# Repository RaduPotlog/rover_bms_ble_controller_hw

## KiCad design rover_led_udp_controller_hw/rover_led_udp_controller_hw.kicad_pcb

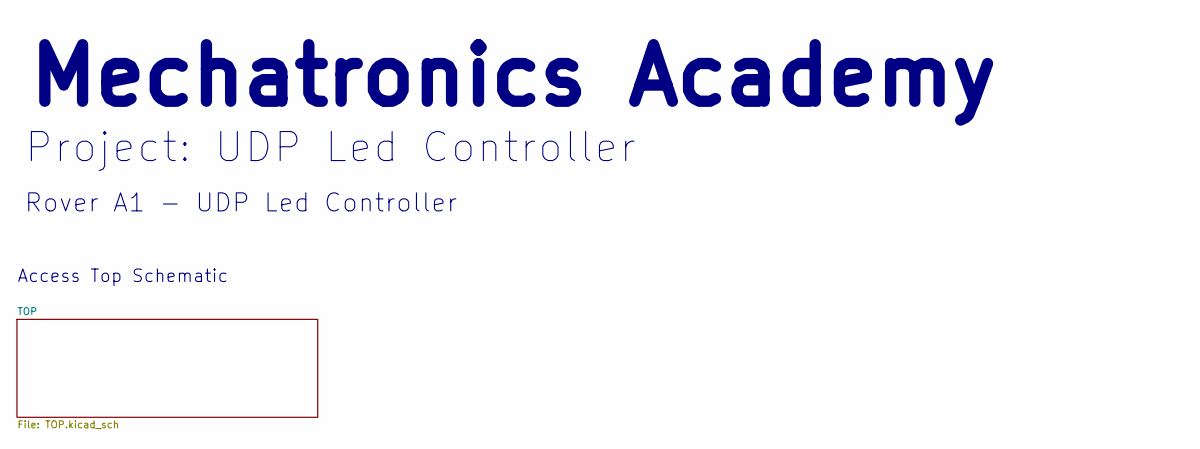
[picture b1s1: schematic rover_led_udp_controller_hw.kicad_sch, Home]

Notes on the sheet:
Rover A1 - UDP Led Controller
Project: UDP Led Controller
Access Top Schematic
Mechatronics Academy

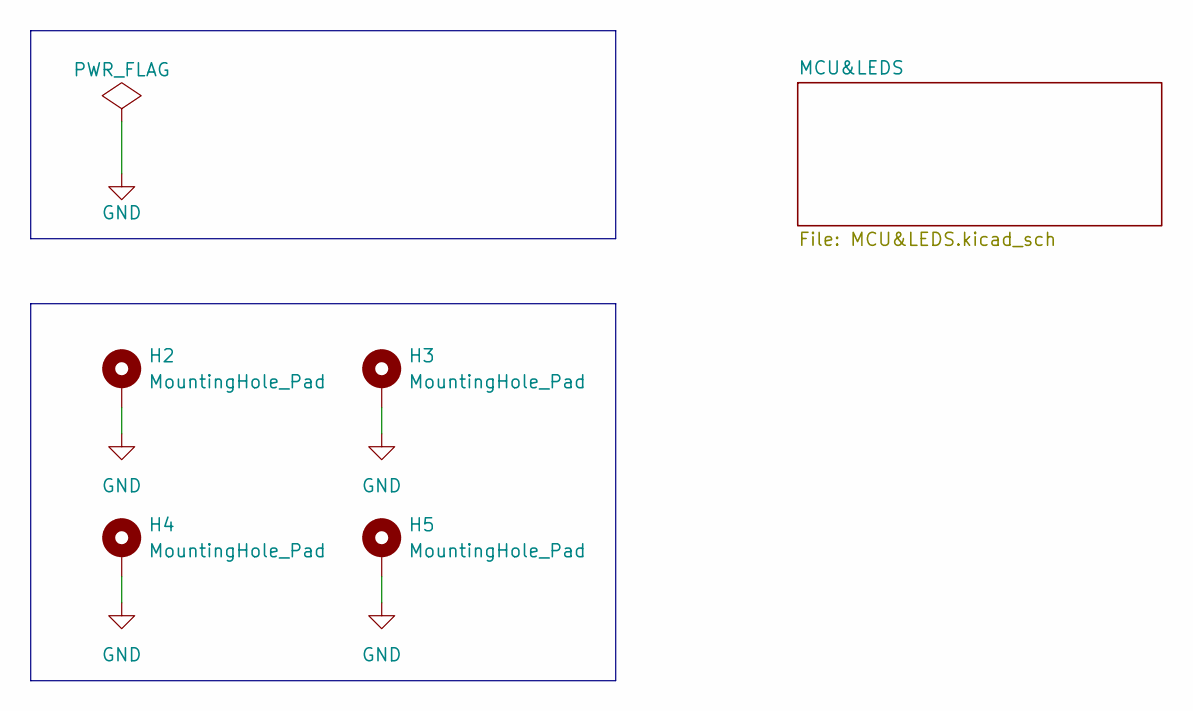
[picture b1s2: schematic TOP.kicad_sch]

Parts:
H2, H3, H4, H5: MountingHole_Pad; MountingHole_2.5mm_Pad_Via

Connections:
GND: H2.1 (1_1), H3.1 (1_1), H4.1 (1_1), H5.1 (1_1); also elsewhere on the board

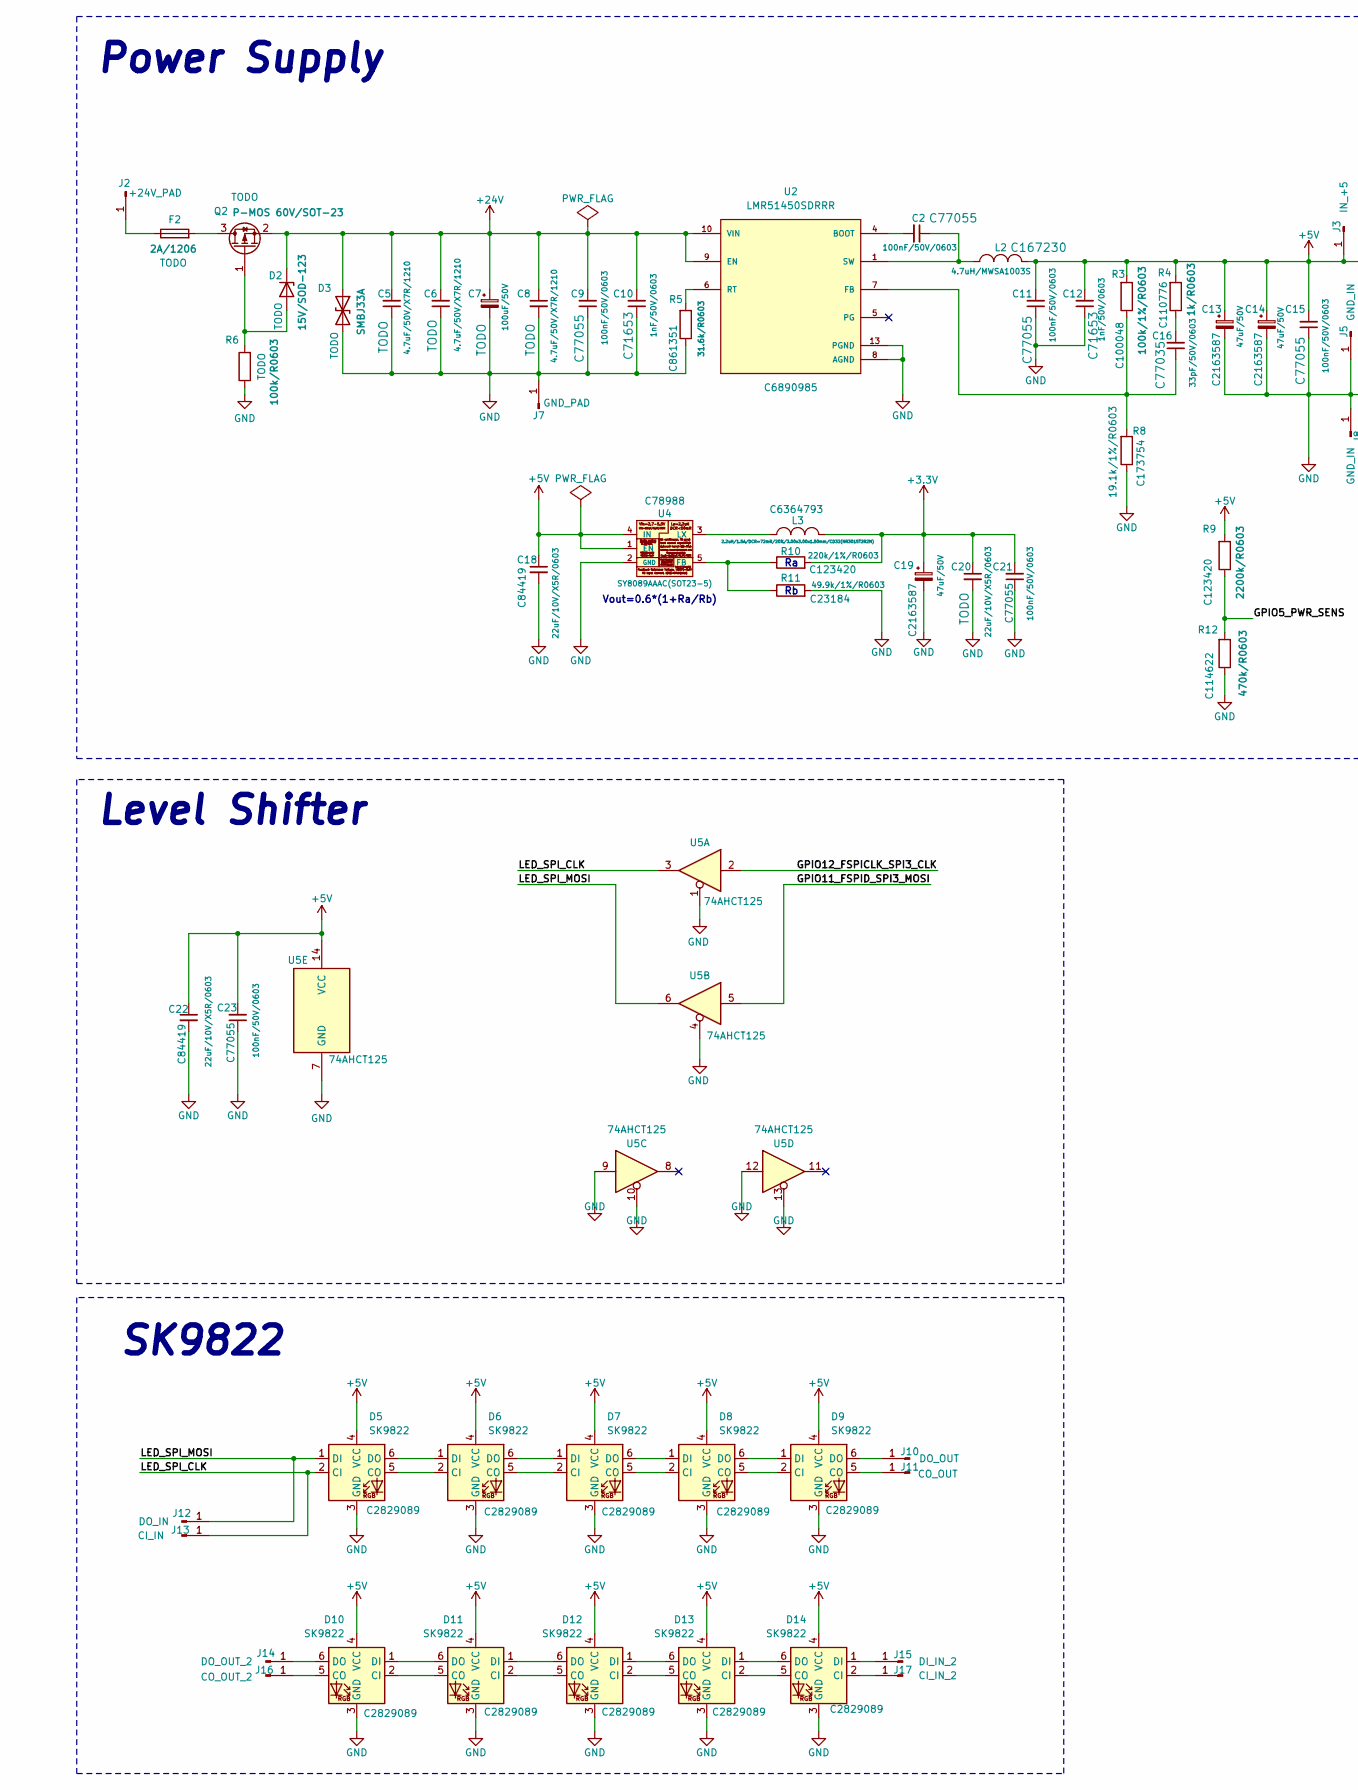
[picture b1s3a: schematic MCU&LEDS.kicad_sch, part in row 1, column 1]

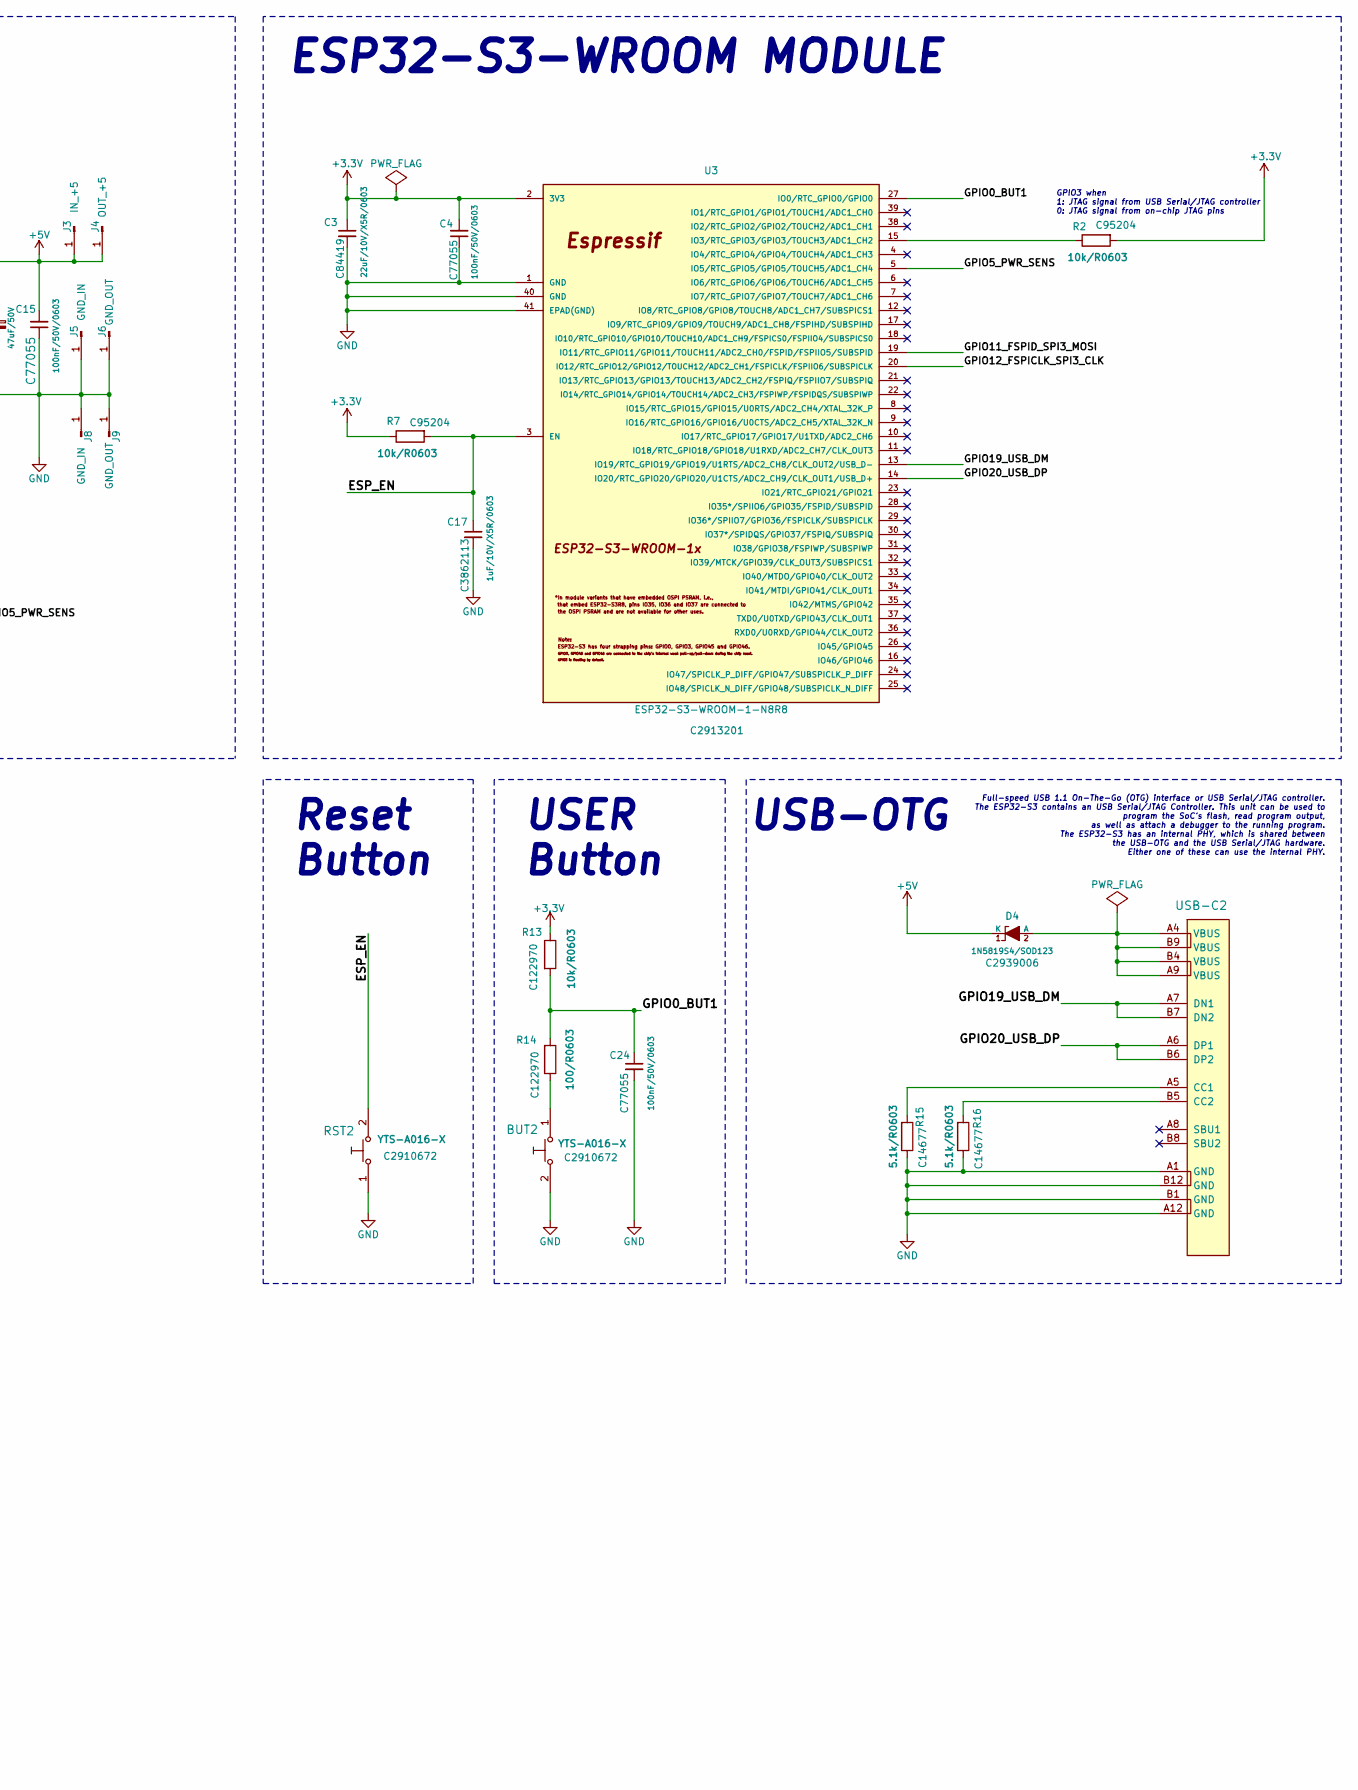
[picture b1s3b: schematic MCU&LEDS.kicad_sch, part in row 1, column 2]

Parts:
BUT2: YTS-A016-X; JLCPCB C2910672
C2, C4, C9, C11, C15, C21, C23, C24: 100nF/50V/0603; C_0603_1608Metric; JLCPCB C77055
C3, C18, C22: 22uF/10V/X5R/0603; C_0603_1608Metric; JLCPCB C84419
C5, C6, C8: 4.7uF/50V/X7R/1210; C_1210_3225Metric; JLCPCB TODO
C7: 100uF/50V; CP_Elec_8x10.5; JLCPCB TODO
C10, C12: 1nF/50V/0603; C_0603_1608Metric; JLCPCB C71653
C13, C14, C19: 47uF/50V; CP_Elec_6.3x7.7; JLCPCB C2163587
C16: 33pF/50V/0603; C_0603_1608Metric; JLCPCB C77035
C17: 1uF/10V/X5R/0603; C_0603_1608Metric; JLCPCB C3862113
C20: 22uF/10V/X5R/0603; C_0603_1608Metric; JLCPCB TODO
D2: 15V/SOD-123; D_SOD-123; JLCPCB TODO
D3: SMBJ33A; D_SMB; JLCPCB TODO
D4: 1N5819S4/SOD123; SOD-123_1C-2A_KA; JLCPCB C2939006
D5, D6, D7, D8, D9, D10, D11, D12, D13, D14: SK9822; LED_RGB_5050-6; JLCPCB C2829089
F2: 2A/1206; Fuse_1206_3216Metric; JLCPCB TODO
J2: +24V_PAD; TestPoint_Pad_1
J3: IN_+5; TestPoint_Pad_1
J4: OUT_+5; TestPoint_Pad_1
J5, J8: GND_IN; TestPoint_Pad_1
J6, J9: GND_OUT; TestPoint_Pad_1
J7: GND_PAD; TestPoint_Pad_1
J10: DO_OUT; TestPoint_Pad
J11: CO_OUT; TestPoint_Pad
J12: DO_IN; TestPoint_Pad
J13: CI_IN; TestPoint_Pad
J14: DO_OUT_2; TestPoint_Pad
J15: DI_IN_2; TestPoint_Pad
J16: CO_OUT_2; TestPoint_Pad
J17: CI_IN_2; TestPoint_Pad
L2: 4.7uH/MWSA1003S; L_Sunlord_MWSA1003S; JLCPCB C167230
L3: 2.2uH/1.5A/DCR=72mR/20%/3.00x3.00x1.50mm/CD32(NR3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; CD32; JLCPCB C6364793
Q2: P-MOS 60V/SOT-23; SOT-23; JLCPCB TODO
R2, R7: 10k/R0603; R_0603_1608Metric_Pad0.98x0.95mm_HandSolder; JLCPCB C95204
R3: 100k/1%/R0603; R_0603_1608Metric_Pad0.98x0.95mm_HandSolder; JLCPCB C100048
R4: 1k/R0603; R_0603_1608Metric_Pad0.98x0.95mm_HandSolder; JLCPCB C110776
R5: 31.6k/R0603; R_0603_1608Metric_Pad0.98x0.95mm_HandSolder; JLCPCB C861351
R6: 100k/R0603; R_0603_1608Metric_Pad0.98x0.95mm_HandSolder; JLCPCB TODO
R8: 19.1k/1%/R0603; R_0603_1608Metric_Pad0.98x0.95mm_HandSolder; JLCPCB C173754
R9: 2200k/R0603; R_0603_1608Metric_Pad0.98x0.95mm_HandSolder; JLCPCB C123420
R10: 220k/1%/R0603; R_0603_1608Metric_Pad0.98x0.95mm_HandSolder; JLCPCB C123420
R11: 49.9k/1%/R0603; R_0603_1608Metric_Pad0.98x0.95mm_HandSolder; JLCPCB C23184
R12: 470k/R0603; R_0603_1608Metric_Pad0.98x0.95mm_HandSolder; JLCPCB C114622
R13: 10k/R0603; R_0603_1608Metric_Pad0.98x0.95mm_HandSolder; JLCPCB C122970
R14: 100/R0603; R_0603_1608Metric_Pad0.98x0.95mm_HandSolder; JLCPCB C122970
R15, R16: 5.1k/R0603; R_0603_1608Metric_Pad0.98x0.95mm_HandSolder; JLCPCB C14677
RST2: YTS-A016-X; JLCPCB C2910672
U2: LMR51450SDRRR; PARTREV December 2022; JLCPCB C6890985
U3: ESP32-S3-WROOM-1-N8R8; ESP32-­S3-­WROOM­-1; JLCPCB C2913201
U4: SY8089AAAC(SOT23-5); SOT-23-5; JLCPCB C78988
U5: 74AHCT125; SOIC-14_3.9x8.7mm_P1.27mm
USB-C2: USB2.0_TYPE-C(A40-00119-A52-12); USB2.0_TYPE-C-ONLY-PADS

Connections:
+3.3V: C3.1, C4.2, C19.1, C20.1, C21.2, L3.2, R2.2, R7.1, R10.2, R13.1, U3.2 (3V3)
+5V: C11.2, C12.2, C13.1, C14.1, C15.2, C18.1, C22.1, C23.2, D4.1 (K), D5.4 (VCC), D6.4 (VCC), D7.4 (VCC), D8.4 (VCC), D9.4 (VCC), D10.4 (VCC), D11.4 (VCC), D12.4 (VCC), D13.4 (VCC), D14.4 (VCC), J3.1 (Pin_1_1), J4.1 (Pin_1_1), L2.2, R3.2, R4.2, R9.2, U4.1 (EN), U4.4 (IN), U5.14 (VCC)
+24V: C5.2, C6.2, C7.1, C8.1, C9.2, C10.2, D2.1 (K), D3.1 (A1), Q2.2 (S), U2.9 (EN), U2.10 (VIN), U2.11 (VIN), U2.12 (VIN)
/TOP/MCU&LEDS/ESP_EN: C17.1, R7.2, RST2.2, U3.3 (EN)
/TOP/MCU&LEDS/GPIO0_BUT1: C24.1, R13.2, R14.2, U3.27 (IO0/RTC_GPIO0/GPIO0)
/TOP/MCU&LEDS/GPIO5_PWR_SENS: R9.1, R12.2, U3.5 (IO5/RTC_GPIO5/GPIO5/TOUCH5/ADC1_CH4)
/TOP/MCU&LEDS/GPIO11_FSPID_SPI3_MOSI: U3.19 (IO11/RTC_GPIO11/GPIO11/TOUCH11/ADC2_CH0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), U5.5
/TOP/MCU&LEDS/GPIO12_FSPICLK_SPI3_CLK: U3.20 (IO12/RTC_GPIO12/GPIO12/TOUCH12/ADC2_CH1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), U5.2
/TOP/MCU&LEDS/GPIO19_USB_DM: U3.13 (IO19/RTC_GPIO19/GPIO19/U1RTS/ADC2_CH8/C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), USB-C2.A7 (DN1), USB-C2.B7 (DN2)
/TOP/MCU&LEDS/GPIO20_USB_DP: U3.14 (IO20/RTC_GPIO20/GPIO20/U1CTS/ADC2_CH9/C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), USB-C2.A6 (DP1), USB-C2.B6 (DP2)
/TOP/MCU&LEDS/LED_SPI_CLK: D5.2 (CI), J13.1 (Pin_1_1), U5.3
/TOP/MCU&LEDS/LED_SPI_MOSI: D5.1 (DI), J12.1 (Pin_1_1), U5.6
GND: BUT2.2, C3.2, C4.1, C5.1, C6.1, C7.2, C8.2, C9.1, C10.1, C11.1, C12.1, C13.2, C14.2, C15.1, C17.2, C18.2, C19.2, C20.2, C21.1, C22.2, C23.1, C24.2, D3.2 (A2), D5.3 (GND), D6.3 (GND), D7.3 (GND), D8.3 (GND), D9.3 (GND), D10.3 (GND), D11.3 (GND), D12.3 (GND), D13.3 (GND), D14.3 (GND), J5.1 (Pin_1_1), J6.1 (Pin_1_1), J7.1 (Pin_1_1), J8.1 (Pin_1_1), J9.1 (Pin_1_1), R5.1, R6.1, R8.1, R11.2, R12.1, R15.1, R16.1, RST2.1, U2.8 (AGND), U2.13 (PGND), U3.1 (GND), U3.40 (GND), U3.41 (EPAD(GND)), U4.2 (GND), U5.1, U5.4, U5.7 (GND), U5.9, U5.10, U5.12, U5.13, USB-C2.A1 (GND), USB-C2.A12 (GND), USB-C2.B1 (GND), USB-C2.B12 (GND); also elsewhere on the board
unnamed: BUT2.1, R14.1
unnamed: C2.1, L2.1, U2.1 (SW), U2.2 (SW), U2.3 (SW)
unnamed: C16.2, R4.1
unnamed: D2.2 (A), Q2.1 (G), R6.2
unnamed: D4.2 (A), USB-C2.A4 (VBUS), USB-C2.A9 (VBUS), USB-C2.B4 (VBUS), USB-C2.B9 (VBUS)
unnamed: D5.5 (CO), D6.2 (CI)
unnamed: D5.6 (DO), D6.1 (DI)
unnamed: D6.5 (CO), D7.2 (CI)
unnamed: D6.6 (DO), D7.1 (DI)
unnamed: D7.5 (CO), D8.2 (CI)
unnamed: D7.6 (DO), D8.1 (DI)
unnamed: D8.5 (CO), D9.2 (CI)
unnamed: D8.6 (DO), D9.1 (DI)
unnamed: D9.5 (CO), J11.1 (Pin_1_1)
unnamed: D9.6 (DO), J10.1 (Pin_1_1)
unnamed: D10.2 (CI), D11.5 (CO)
unnamed: D10.5 (CO), J16.1 (Pin_1_1)
unnamed: D10.1 (DI), D11.6 (DO)
unnamed: D10.6 (DO), J14.1 (Pin_1_1)
unnamed: D11.2 (CI), D12.5 (CO)
unnamed: D11.1 (DI), D12.6 (DO)
unnamed: D12.2 (CI), D13.5 (CO)
unnamed: D12.1 (DI), D13.6 (DO)
unnamed: D13.2 (CI), D14.5 (CO)
unnamed: D13.1 (DI), D14.6 (DO)
unnamed: D14.2 (CI), J17.1 (Pin_1_1)
unnamed: D14.1 (DI), J15.1 (Pin_1_1)
unnamed: F2.1, J2.1 (Pin_1_1)
unnamed: F2.2, Q2.3 (D)
unnamed: C2.2, U2.4 (BOOT)
unnamed: C16.1, R3.1, R8.2, U2.7 (FB)
unnamed: R5.2, U2.6 (RT)
unnamed: R2.1, U3.15 (IO3/RTC_GPIO3/GPIO3/TOUCH3/ADC1_CH2)
unnamed: R10.1, R11.1, U4.5 (FB)
unnamed: L3.1, U4.3 (LX)
unnamed: R15.2, USB-C2.A5 (CC1)
unnamed: R16.2, USB-C2.B5 (CC2)

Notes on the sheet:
ESP32-S3-WROOM MODULE
Power Supply
Full-speed USB 1.1 On-The-Go (OTG) interface or USB Serial/JTAG controller. The ESP32-S3 contains an USB Serial/JTAG Controller. This unit can be used to program the SoC’s flash, read program output, as well as attach a debugger to the running program. The ESP32-S3 has an internal PHY, which is sha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
Vout=0.6*(1+Ra/Rb)
GPIO3 when 1: JTAG signal from USB Serial/JTAG controller 0: JTAG signal from on-chip JTAG pins
Reset Button
USB-OTG
Level Shifter
SK9822
USER Button

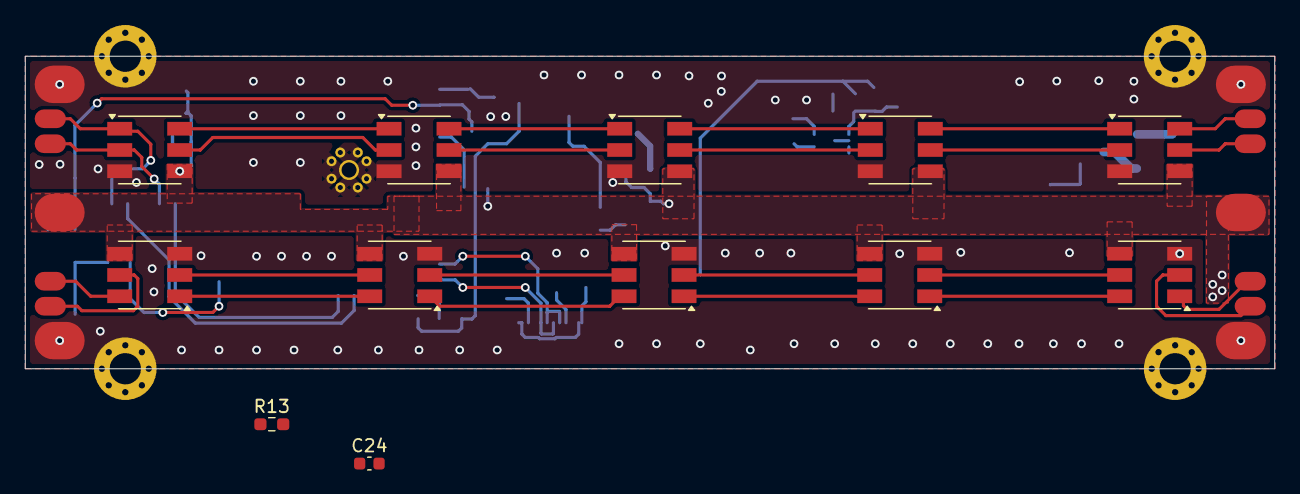
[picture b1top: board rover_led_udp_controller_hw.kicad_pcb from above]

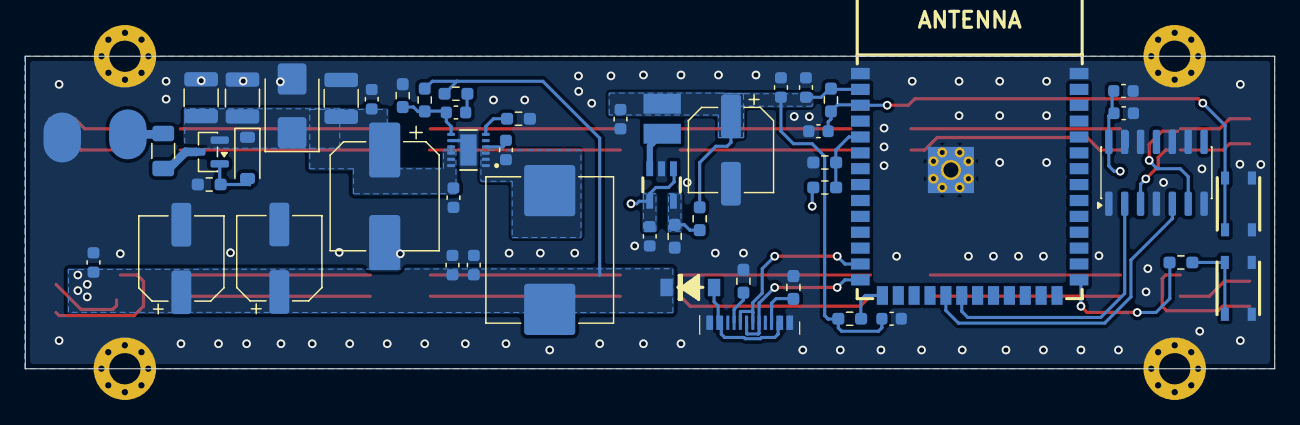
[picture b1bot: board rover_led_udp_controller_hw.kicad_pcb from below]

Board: 2 copper layers, 100.0 x 25.0 mm, 82 parts (52 on the bottom side), 50 nets.
